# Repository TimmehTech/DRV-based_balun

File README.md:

# DRV-based_balun
An unbalanced to balanced audio conversion circuit based on the DRV134

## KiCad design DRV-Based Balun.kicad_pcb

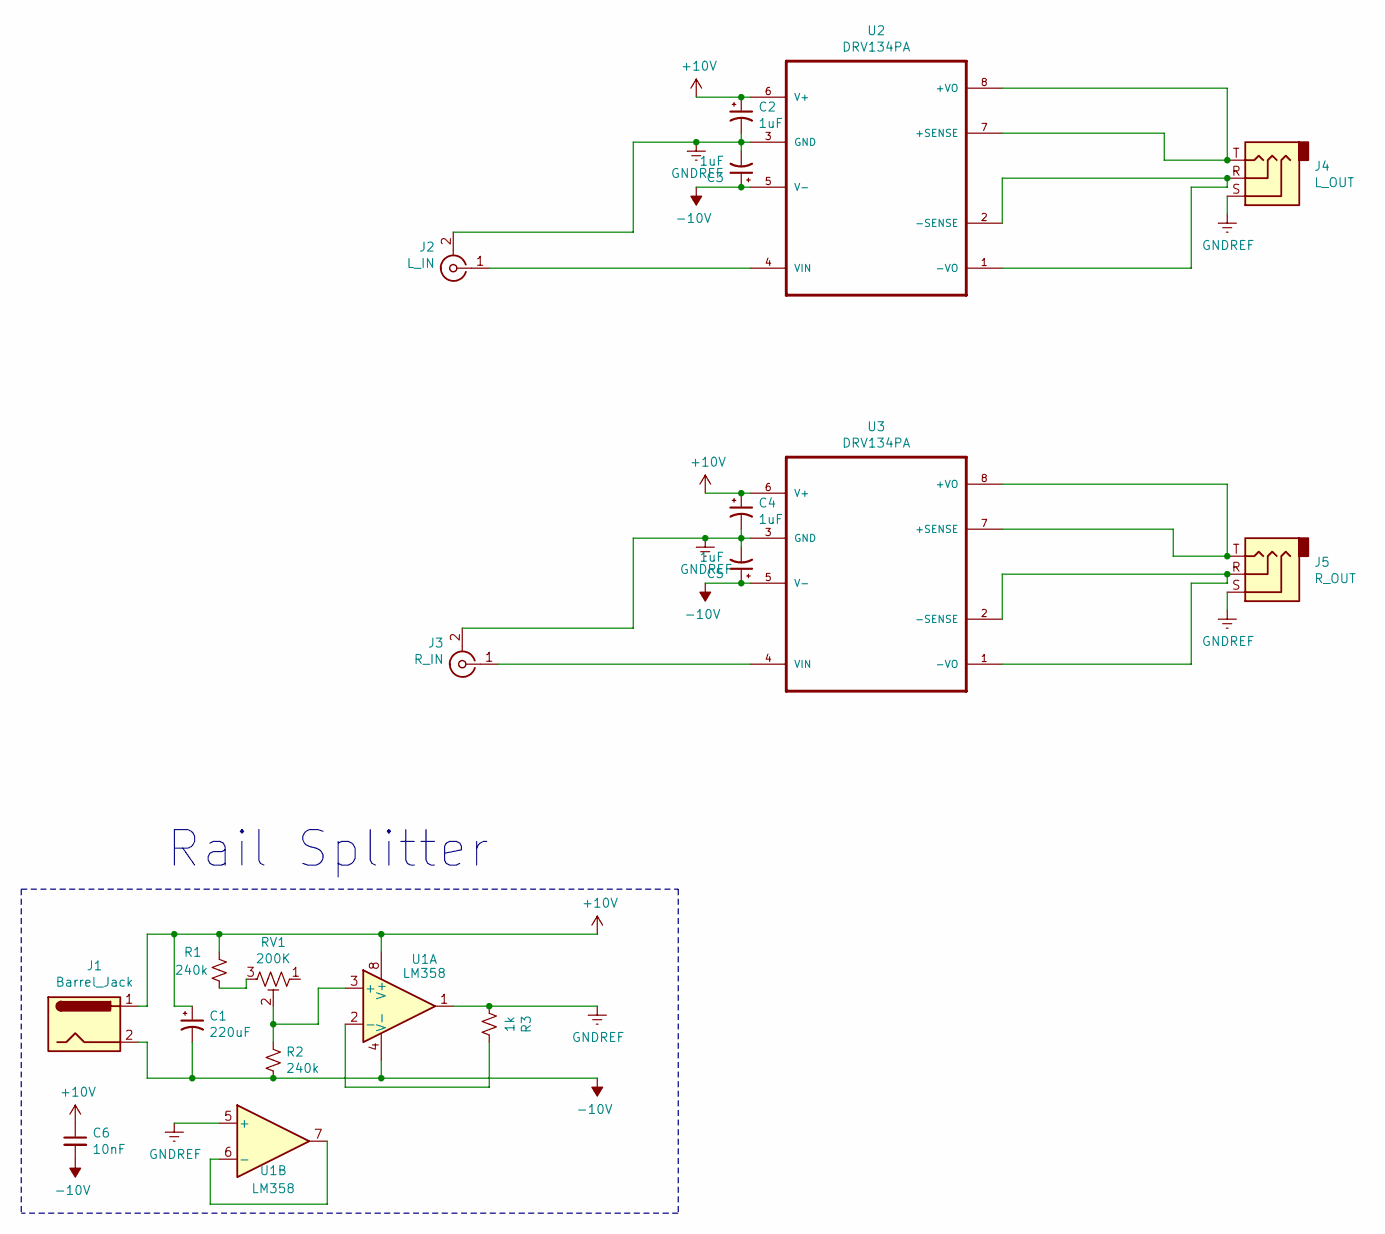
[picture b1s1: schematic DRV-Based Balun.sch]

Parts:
C1: 220uF; CP_Radial_D8.0mm_P3.50mm
C2, C3, C4, C5: 1uF; C_Disc_D4.7mm_W2.5mm_P5.00mm
C6: 10nF; C_Disc_D6.0mm_W2.5mm_P5.00mm
J1: Barrel_Jack; PinHeader_1x02_P2.54mm_Vertical
J2: L_IN; PinHeader_1x02_P2.54mm_Vertical
J3: R_IN; PinHeader_1x02_P2.54mm_Vertical
J4: L_OUT; PinHeader_1x03_P2.54mm_Vertical_TRS
J5: R_OUT; PinHeader_1x03_P2.54mm_Vertical_TRS
R1, R2: 240k; R_Axial_DIN0207_L6.3mm_D2.5mm_P10.16mm_Horizontal
R3: 1k; R_Axial_DIN0207_L6.3mm_D2.5mm_P10.16mm_Horizontal
RV1: 200K; Potentiometer_Bourns_3296W_Vertical
U1: LM358; DIP-8_W7.62mm
U2, U3: DRV134PA; DIP254P762X508-8

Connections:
+10V: C1.1, C2.1, C4.1, C6.1, J1.1, R1.1, U1.8 (V+), U2.6 (V+), U3.6 (V+)
-10V: C1.2, C3.1, C5.1, C6.2, J1.2, R2.2, U1.4 (V-), U2.5 (V-), U3.5 (V-)
GNDREF: C2.2, C3.2, C4.2, C5.2, J2.2 (Ext), J3.2 (Ext), J4.S, J5.S, R3.2, U1.1, U1.5 (+), U2.3 (GND), U3.3 (GND)
unnamed: J2.1 (In), U2.4 (VIN)
unnamed: J3.1 (In), U3.4 (VIN)
unnamed: J4.R, U2.1 (-VO), U2.2 (-SENSE)
unnamed: J4.T, U2.7 (+SENSE), U2.8 (+VO)
unnamed: J5.R, U3.1 (-VO), U3.2 (-SENSE)
unnamed: J5.T, U3.7 (+SENSE), U3.8 (+VO)
unnamed: R1.2, RV1.3
unnamed: R2.1, RV1.2, U1.3 (+)
unnamed: R3.1, U1.2 (-)
unnamed: U1.6 (-), U1.7

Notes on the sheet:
Rail Splitter

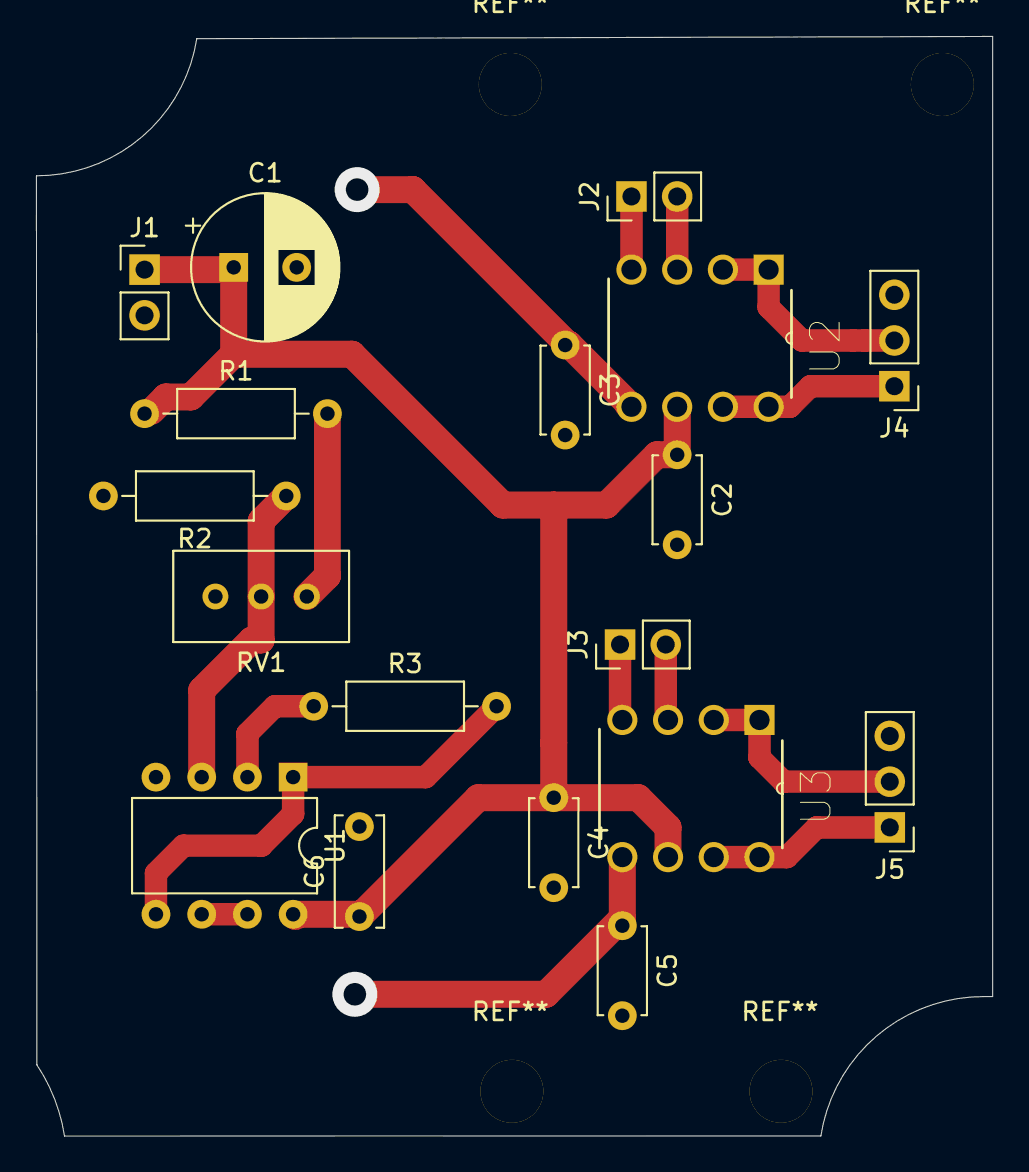
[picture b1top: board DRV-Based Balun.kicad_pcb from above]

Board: 2 copper layers, 53.1 x 61.1 mm, 18 parts (0 on the bottom side), 13 nets.

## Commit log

2020-04-25 Inital upload of breadboarded but not complete project.
